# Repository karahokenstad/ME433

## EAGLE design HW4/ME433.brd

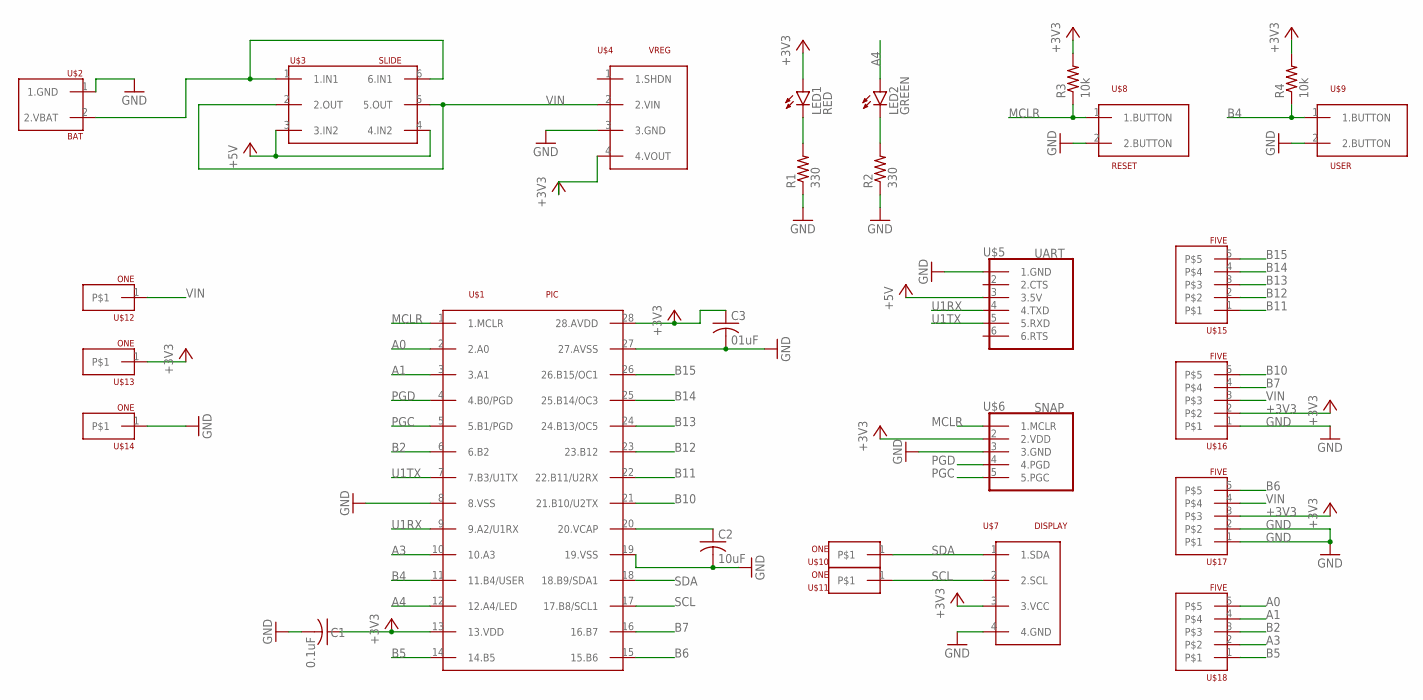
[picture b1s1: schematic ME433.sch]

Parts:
C1: 0.1uF; C025-024X044
C2: 10uF; C025-024X044
C3: 01uF; C025-024X044
LED1: RED; LED3MM
LED2: GREEN; LED3MM
R1, R2: 330; 0207/7
R3, R4: 10k; 0207/7
U$1: PIC; DIL28-3
U$2: BAT
U$3: SLIDE
U$4: VREG
U$5: UART
U$6: SNAP
U$7: DISPLAY
U$8: RESET; BUTTON
U$9: USER; BUTTON
U$10, U$11, U$12, U$13, U$14: ONE
U$15, U$16, U$17, U$18: FIVE

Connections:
+3V3: C1.1, C3.1, LED1.A, R3.2, R4.2, U$1.13 (13.VDD), U$1.28 (28.AVDD), U$4.4 (4.VOUT), U$6.2 (2.VDD), U$7.3 (3.VCC), U$13.1, U$16.2, U$17.3
+5V: U$3.3 (3.IN2), U$3.4 (4.IN2), U$5.3 (3.5V)
A0: U$1.2 (2.A0), U$18.5
A1: U$1.3 (3.A1), U$18.4
A3: U$1.10 (10.A3), U$18.2
A4: LED2.A, U$1.12 (12.A4/LED)
B2: U$1.6 (6.B2), U$18.3
B4: R4.1, U$1.11 (11.B4/USER), U$9.1 (1.BUTTON)
B5: U$1.14 (14.B5), U$18.1
B6: U$1.15 (15.B6), U$17.5
B7: U$1.16 (16.B7), U$16.4
B10: U$1.21 (21.B10/U2TX), U$16.5
B11: U$1.22 (22.B11/U2RX), U$15.1
B12: U$1.23 (23.B12), U$15.2
B13: U$1.24 (24.B13/OC5), U$15.3
B14: U$1.25 (25.B14/OC3), U$15.4
B15: U$1.26 (26.B15/OC1), U$15.5
GND: C1.2, C2.2, C3.2, R1.1, R2.1, U$1.8 (8.VSS), U$1.19 (19.VSS), U$1.27 (27.AVSS), U$2.1 (1.GND), U$4.3 (3.GND), U$5.1 (1.GND), U$6.3 (3.GND), U$7.4 (4.GND), U$8.2 (2.BUTTON), U$9.2 (2.BUTTON), U$14.1, U$16.1, U$17.1, U$17.2
MCLR: R3.1, U$1.1 (1.MCLR), U$6.1 (1.MCLR), U$8.1 (1.BUTTON)
unnamed: LED1.K (C), R1.2
unnamed: U$2.2 (2.VBAT), U$3.1 (1.IN1), U$3.6 (6.IN1)
unnamed: C2.1, U$1.20 (20.VCAP)
unnamed: LED2.K (C), R2.2
PGC: U$1.5 (5.B1/PGD), U$6.5 (5.PGC)
PGD: U$1.4 (4.B0/PGD), U$6.4 (4.PGD)
SCL: U$1.17 (17.B8/SCL1), U$7.2 (2.SCL), U$11.1
SDA: U$1.18 (18.B9/SDA1), U$7.1 (1.SDA), U$10.1
U1RX: U$1.9 (9.A2/U1RX), U$5.4 (4.TXD)
U1TX: U$1.7 (7.B3/U1TX), U$5.5 (5.RXD)
VIN: U$3.2 (2.OUT), U$3.5 (5.OUT), U$4.2 (2.VIN), U$12.1, U$16.3, U$17.4

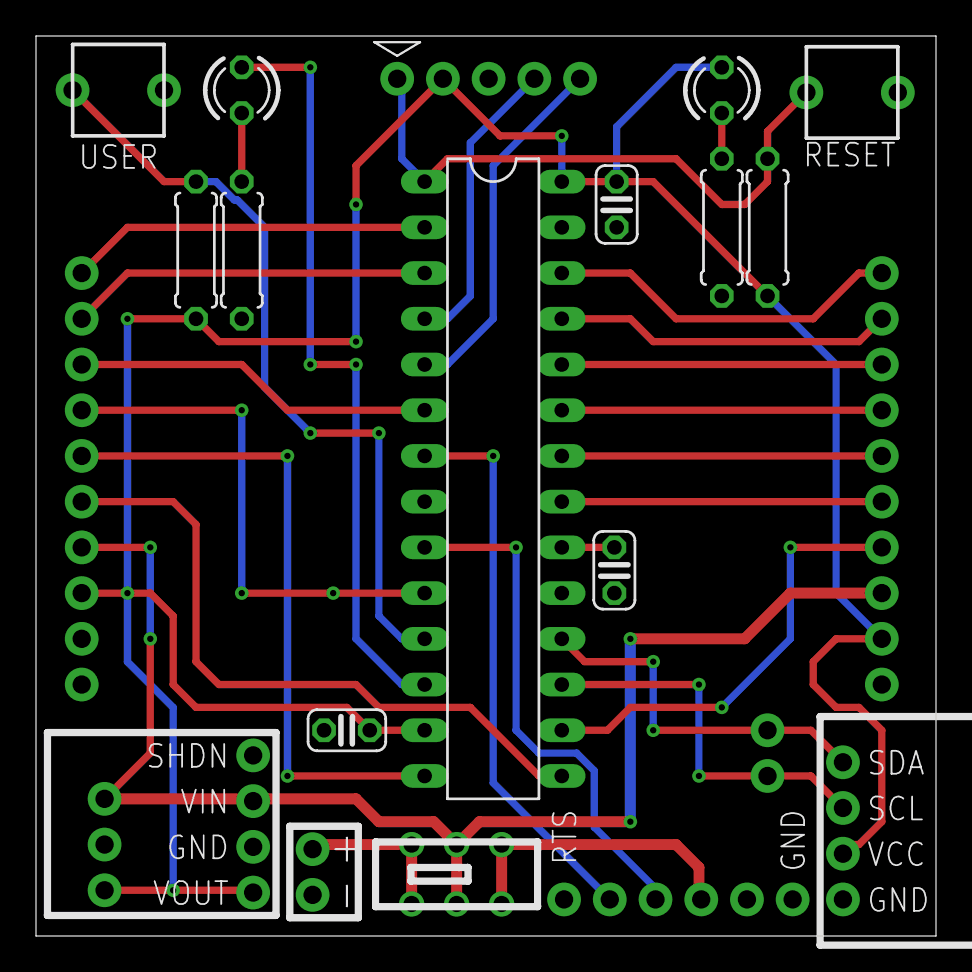
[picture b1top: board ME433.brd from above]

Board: 2 copper layers, 50.0 x 50.0 mm, 27 parts (0 on the bottom side), 30 nets.

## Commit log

2022-04-05 Add pics
2022-04-14 add all files and pics
2022-04-19 Add main code and photo
2022-04-21 Add main and i2c files
2022-05-04 Add c, h files
2022-05-11 add code and pic
2022-05-29 add files
2022-06-07 add c and h files
2022-06-08 add code and pictures
